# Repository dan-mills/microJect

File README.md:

# microJect
MQL lubrication system using automotive injectors to lubricate cutting tools.

Control is via modbus RTU on RS485 or via switches and pots (Two channels only in that mode). 
Power input is 24V and power delivered to the injector heads is 12V at up to about 3A total from an on board power converter. 

Firmware is written in Rust with Embassy as the framework and the processor on the board is an STM32F030k6. 

#Electrical Interface 
|           |         |
|----------|----------|
| Power supply | 24V @ 1.5A but usually much less.|
| Injector outputs | 12V @1A, 3A total max | 
| Digital inputs | 2 Opto isolated, 24V max |
| Analogue inputs | 2, 3.3V max, intended for potentiometers|
| Serial interface | Isolated RS485 |

# Operating modes
There is a 4 way dip switch on the board which configure the operating modes
| Switch | Function |
|--------|----------|
| 1 | Enables local control mode, the opto inputs and analog control the first two channels|
| 2| Modbus alternate address, sets the modbus address to be 9 instead of 8 |
| 3, 4| Modbus baud rate| 

Baud rates
| SW 3 | SW 4| Baud Rate |
|------|-----|-----------|
| Off | Off | 4800 |
| Off | On | 9600 |
| On | Off | 19200 |
| On | On | 115200 |

# Modbus support

Modbus interface is RTU over RS485 half duplex, formatted as 8-E-1.

Coils
| Coil | Description | 
|------|-------------|
| 1 | Pulse enable for channel 1|
| 2 | Pulse enable for channel 2|
| 3 | Pulse enable for channel 3|
| 4 | Pulse enable for channel 4|

Note in modbus mode the coils will switch off 5 seconds after the last communication is received to avoid spilling coolant everywhere. 

Holding Registers
| Register | Description |
|----------|-------------|
| 1 | Channel 1 pulse length |
| 2 | Channel 1 period |
| 3 | Channel 2 pulse length |
| 4 | Channel 2 period |
| 5 | Channel 3 pulse length |
| 6 | Channel 3 period |
| 7 | Channel 4 pulse length |
| 8 | Channel 4 period |

Discrete inputs
| Input | Description |
|-------|-------------|
| 1 | Enable input for ch1 when in local control mode|
| 2 | Enable input for ch2 when in local control mode|

Analogue inputs 
| Input | Description |
|-------|-------------|
| 1 | 0-3.3V period control input for channel 1 when in local control mode|
| 2 | 0-3.3V period control input for channel 2 when in local control mode|

Both the discrete inputs and the analogue channels can be read over modbus when not using local mode so you can readily use them for other things when using modbus for control.

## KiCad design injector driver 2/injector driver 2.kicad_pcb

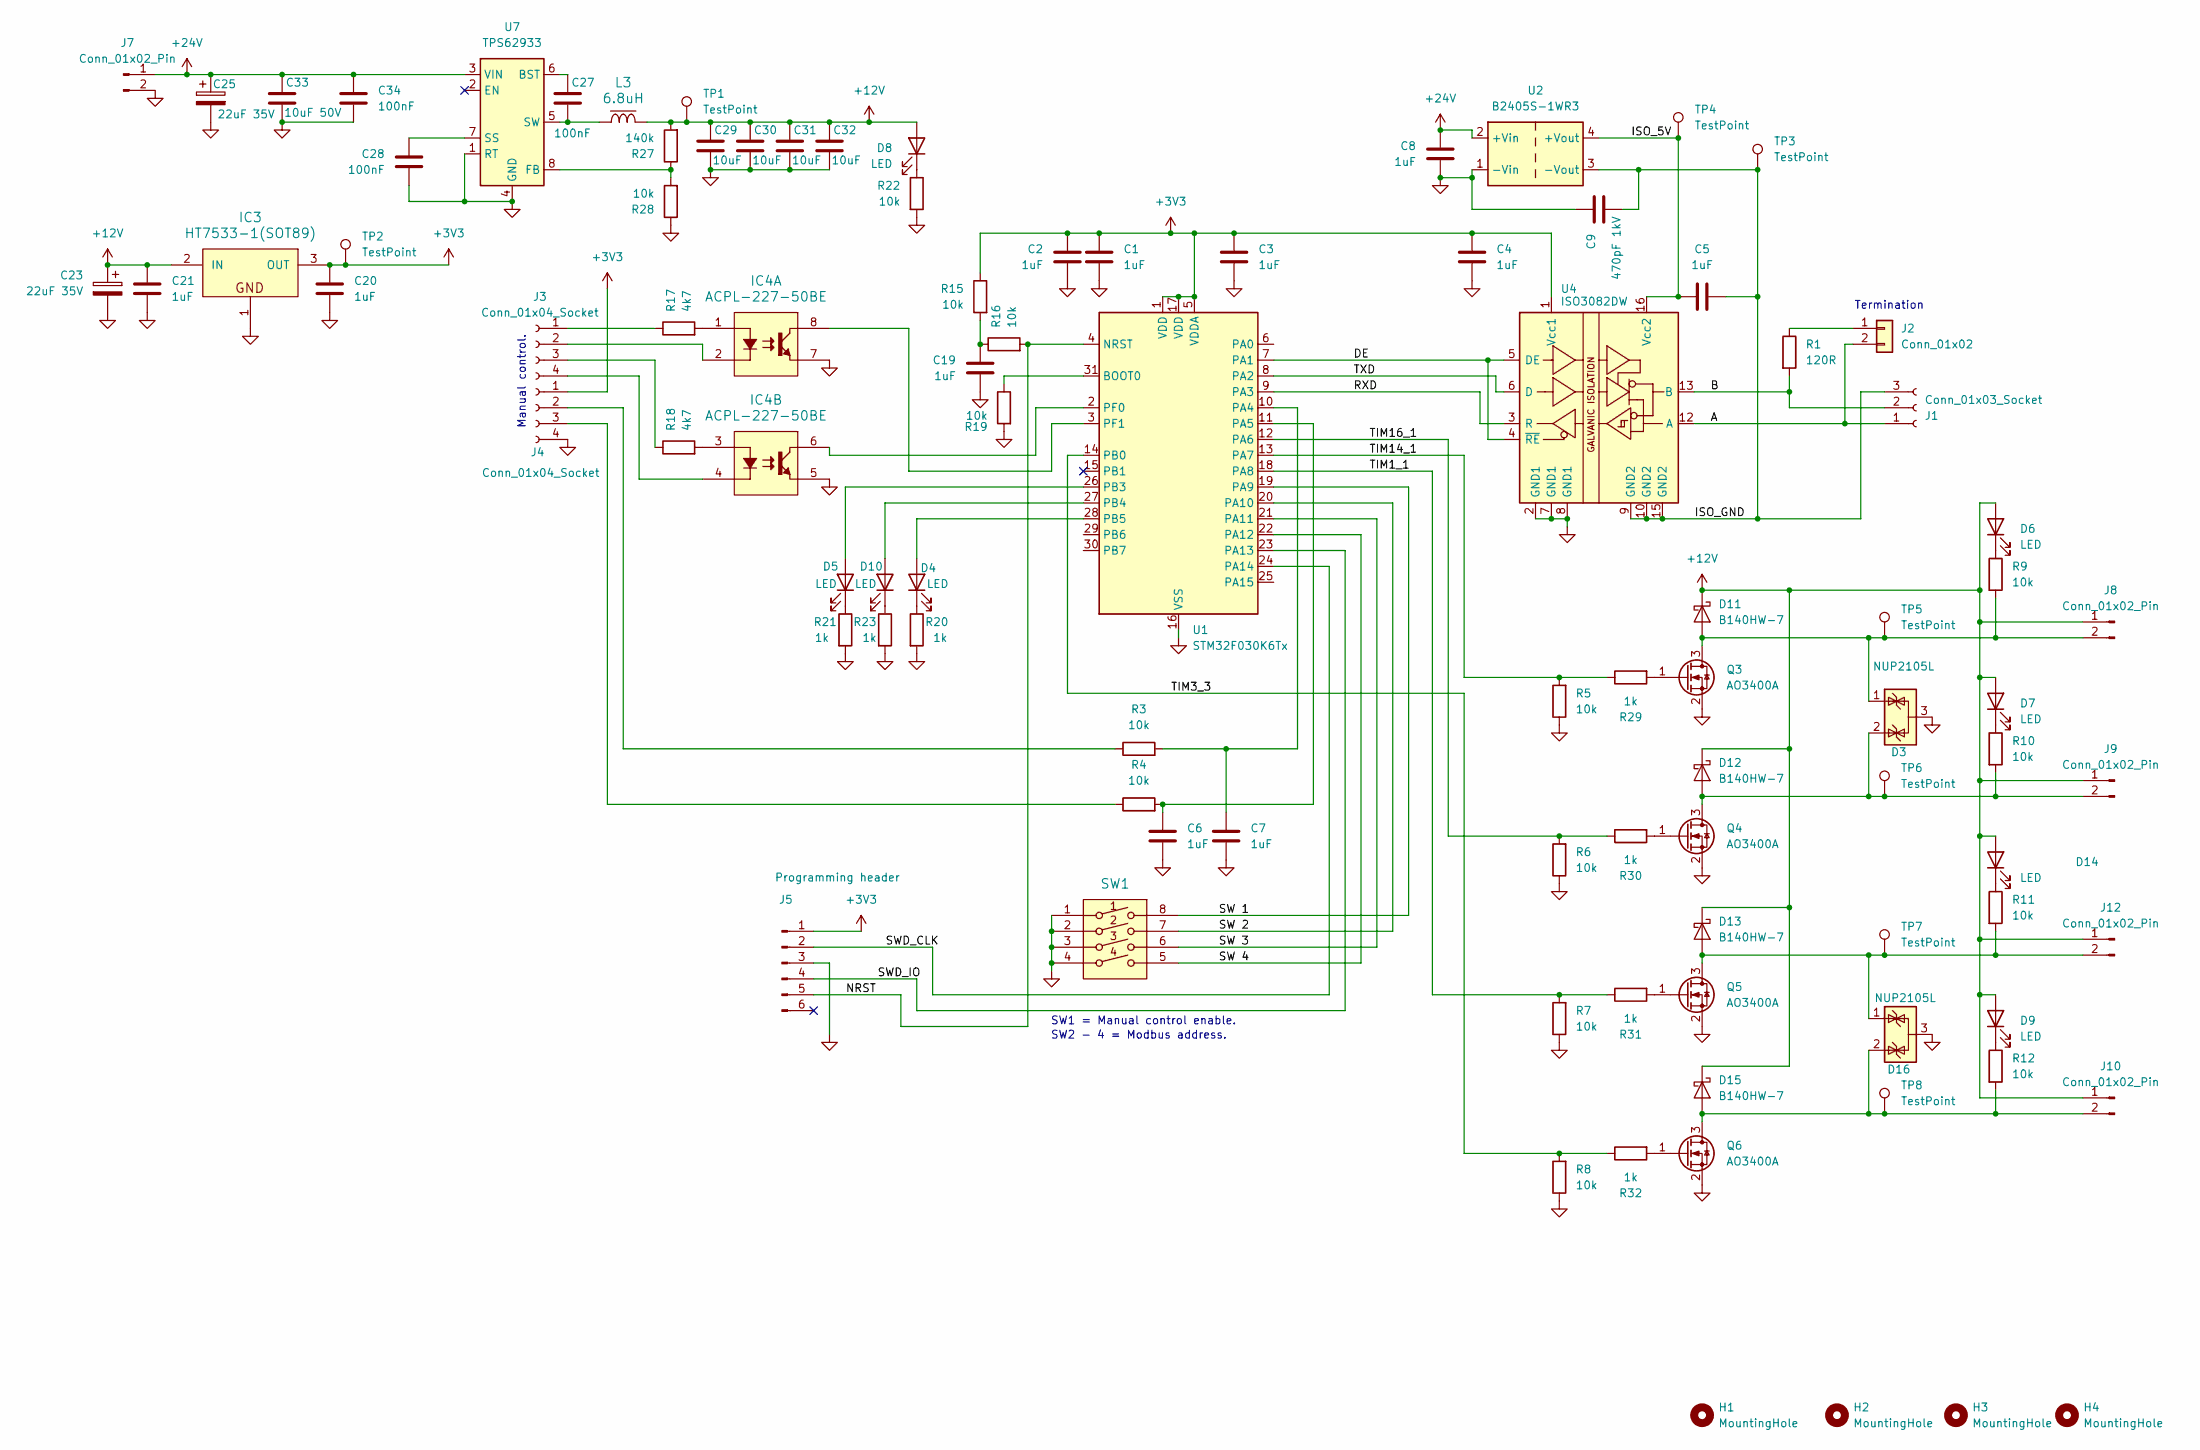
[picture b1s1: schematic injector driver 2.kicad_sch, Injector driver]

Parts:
C1, C2, C3, C4, C5, C6, C7, C8, C19, C20, C21: 1uF; C_0603_1608Metric
C9: 470pF 1kV; C_1206_3216Metric
C23, C25: 22uF 35V; CP_Elec_5x5.7
C27, C28, C34: 100nF; C_0603_1608Metric
C29, C30, C31, C32: 10uF; C_1206_3216Metric
C33: 10uF 50V; C_1206_3216Metric
D3, D16: NUP2105L; SOT-23
D4, D5, D6, D7, D8, D9, D10, D14: LED; LED_0603_1608Metric
D11, D12, D13, D15: B140HW-7; D_SOD-123; Part Number B140HW-7; JLCPCB ID C134429
H1, H2, H3, H4: MountingHole; MountingHole_3.2mm_M3_ISO14580_Pad
IC3: HT7533-1(SOT89); SOT89; Part Number HT7533-1(SOT89)
IC4: ACPL-227-50BE; SOIC127P700X220-8N; Part Description DC Input Dual Channel Half-Pitch Photot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
J1: Conn_01x03_Socket; PHOENIX_1751109
J2: Conn_01x02; PinHeader_1x02_P2.54mm_Vertical; Part Number 1-0201FBV0T
J3, J4: Conn_01x04_Socket; PHOENIX_1751112
J5: Programming header; PinHeader_1x06_P2.54mm_Vertical
J7, J8, J9, J10, J12: Conn_01x02_Pin; PHOENIX_1751099
L3: 6.8uH; IND_MURATA-PS_4500; Tolerance ±20%; Part Description Low Profile, High Current IHLP® Inductor
Q3, Q4, Q5, Q6: AO3400A; SOT-23
R1: 120R; R_1206_3216Metric
R3, R4, R5, R6, R7, R8, R9, R10, R11, R12, R15, R16, R19, R22, R28: 10k; R_0603_1608Metric
R17, R18: 4k7; R_0603_1608Metric
R20, R21, R23, R29, R30, R31, R32: 1k; R_0603_1608Metric
R27: 140k; R_0603_1608Metric
SW1: Switch; SW_DIPTRONICS_DHA-04TQ; Part Number SW_DIPTRONICS_DHA-04TQ
TP1, TP2, TP3, TP4, TP5, TP6, TP7, TP8: TestPoint; TestPoint_THTPad_2.5x2.5mm_Drill1.2mm
U1: STM32F030K6Tx; LQFP-32_7x7mm_P0.8mm
U2: B2405S-1WR3; Converter_DCDC_Murata_CRE1xxxxxx3C_THT
U4: ISO3082DW; SOIC-16W_7.5x10.3mm_P1.27mm
U7: TPS62933; SOT-583-8

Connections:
+3V3: C1.1, C2.1, C3.1, C4.1, C20.1, IC3.3 (OUT), J4.1, J5.1, R15.1, TP2.1 (1_1), U1.1 (VDD), U1.5 (VDDA), U1.17 (VDD), U4.1 (Vcc1)
+12V: C21.1, C23.1, C29.1, C30.1, C31.1, C32.1, D6.2 (A), D7.2 (A), D8.2 (A), D9.2 (A), D11.1 (K), D12.1 (K), D13.1 (K), D14.2 (A), D15.1 (K), IC3.2 (IN), J8.1, J9.1, J10.1, J12.1, L3.2, R27.2, TP1.1 (1_1)
+24V: C8.1, C25.1, C33.1, C34.1, J7.1, U2.2 (+Vin), U7.3 (VIN)
/A: J1.1, J2.2, U4.12 (A)
/B: J1.2, R1.2, U4.13 (B)
/DE: U1.7 (PA1), U4.4 (~RE), U4.5 (DE)
/ISO_5V: C5.1, TP4.1 (1_1), U2.4 (+Vout), U4.16 (Vcc2)
/ISO_GND: C5.2, C9.2, J1.3, TP3.1 (1_1), U2.3 (-Vout), U4.9 (GND2), U4.10 (GND2), U4.15 (GND2)
/NRST: J5.5, R16.2, U1.4 (NRST)
/RXD: U1.9 (PA3), U4.3 (R)
/SW 1: SW1.8, U1.19 (PA9)
/SW 2: SW1.7, U1.20 (PA10)
/SW 3: SW1.6, U1.21 (PA11)
/SW 4: SW1.5, U1.22 (PA12)
/SWD_CLK: J5.2, U1.24 (PA14)
/SWD_IO: J5.4, U1.23 (PA13)
/TIM1_1: R7.2, R31.1, U1.18 (PA8)
/TIM3_3: R8.2, R32.1, U1.14 (PB0)
/TIM14_1: R5.2, R29.1, U1.13 (PA7)
/TIM16_1: R6.2, R30.1, U1.12 (PA6)
/TXD: U1.8 (PA2), U4.6 (D)
GND: C1.2, C2.2, C3.2, C4.2, C6.2, C7.2, C8.2, C9.1, C19.2, C20.2, C21.2, C23.2, C25.2, C28.2, C29.2, C30.2, C31.2, C32.2, C33.2, C34.2, D3.3 (A), D16.3 (A), IC3.1 (GND), IC4.5 (E), IC4.7 (E), J4.4, J5.3, J7.2, Q3.2 (S), Q4.2 (S), Q5.2 (S), Q6.2 (S), R5.1, R6.1, R7.1, R8.1, R19.2, R20.2, R21.2, R22.2, R23.2, R28.1, SW1.1, SW1.2, SW1.3, SW1.4, U1.16 (VSS), U1.32 (VSS), U2.1 (-Vin), U4.2 (GND1), U4.7 (GND1), U4.8 (GND1), U7.1 (RT), U7.4 (GND)
unnamed: C19.1, R15.2, R16.1
unnamed: D4.2 (A), U1.28 (PB5)
unnamed: D4.1 (K), R20.1
unnamed: D5.2 (A), U1.26 (PB3)
unnamed: D5.1 (K), R21.1
unnamed: D6.1 (K), R9.1
unnamed: D7.1 (K), R10.1
unnamed: D8.1 (K), R22.1
unnamed: D9.1 (K), R12.1
unnamed: D10.2 (A), U1.27 (PB4)
unnamed: D10.1 (K), R23.1
unnamed: D3.1 (K), D11.2 (A), J8.2, Q3.3 (D), R9.2, TP5.1 (1_1)
unnamed: D3.2 (K), D12.2 (A), J9.2, Q4.3 (D), R10.2, TP6.1 (1_1)
unnamed: D13.2 (A), D16.1 (K), J12.2, Q5.3 (D), R11.2, TP7.1 (1_1)
unnamed: D14.1 (K), R11.1
unnamed: D15.2 (A), D16.2 (K), J10.2, Q6.3 (D), R12.2, TP8.1 (1_1)
unnamed: IC4.1 (A), R17.2
unnamed: IC4.8 (C), U1.3 (PF1)
unnamed: IC4.2 (K), J3.2
unnamed: IC4.3 (A), R18.2
unnamed: IC4.6 (C), U1.2 (PF0)
unnamed: IC4.4 (K), J3.4
unnamed: J2.1, R1.1
unnamed: J3.1, R17.1
unnamed: J3.3, R18.1
unnamed: J4.2, R3.1
unnamed: J4.3, R4.1
unnamed: Q3.1 (G), R29.2
unnamed: Q4.1 (G), R30.2
unnamed: Q5.1 (G), R31.2
unnamed: Q6.1 (G), R32.2
unnamed: R19.1, U1.31 (BOOT0)
unnamed: C7.1, R3.2, U1.10 (PA4)
unnamed: C6.1, R4.2, U1.11 (PA5)
unnamed: C27.1, U7.6 (BST)
unnamed: R27.1, R28.2, U7.8 (FB)
unnamed: C28.1, U7.7 (SS)
unnamed: C27.2, L3.1, U7.5 (SW)

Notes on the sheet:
SW1 = Manual control enable.
Termination
Manual control.
SW2 - 4 = Modbus address.

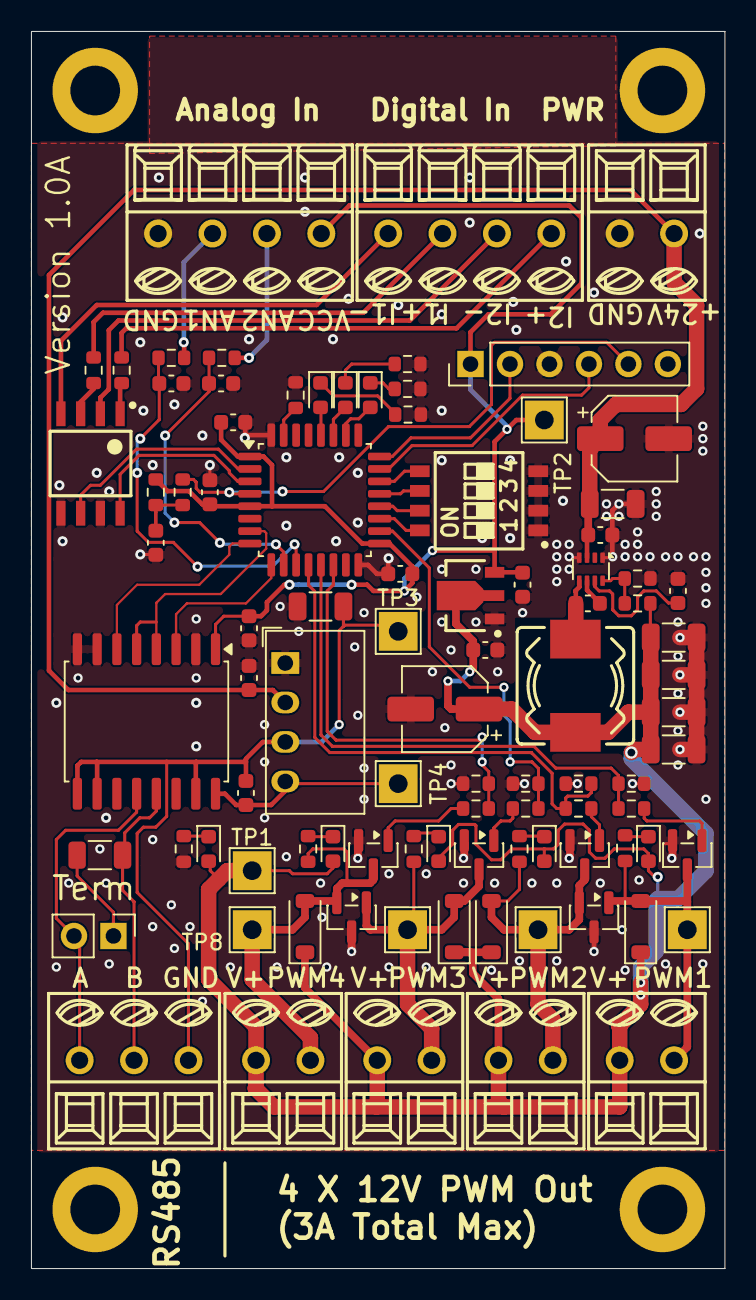
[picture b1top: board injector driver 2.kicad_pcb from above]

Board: 2 copper layers, 44.6 x 79.6 mm, 96 parts (0 on the bottom side), 60 nets.

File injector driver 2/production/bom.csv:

Designator,Footprint,Quantity,Value,LCSC Part #
"C1, C19, C2, C20, C21, C3, C4, C5, C6, C7, C8",0603,11,1uF,
"C23, C25",CP_Elec_5x5.7,2,22uF 35V,
"C27, C28, C34",0603,3,100nF,
"C29, C30, C31, C32",1206,4,10uF,
C33,1206,1,10uF 50V,
C9,1206,1,470pF 1kV,
"D10, D14, D4, D5, D6, D7, D8, D9",0603,8,LED,
"D11, D12, D13, D15",D_SOD-123,4,B140HW-7,
"D16, D3",SOT-23,2,NUP2105L,
IC3,SOT89,1,HT7533-1(SOT89),
IC4,SOIC127P700X220-8N,1,ACPL-227-50BE,
J1,PHOENIX_1751109,1,Conn_01x03_Socket,
"J10, J12, J7, J8, J9",PHOENIX_1751099,5,Conn_01x02_Pin,
J2,PinHeader_1x02_P2.54mm_Vertical,1,Conn_01x02,
"J3, J4",PHOENIX_1751112,2,Conn_01x04_Socket,
J5,PinHeader_1x06_P2.54mm_Vertical,1,Programming header,
L3,IND_MURATA-PS_4500,1,6.8uH,
"Q3, Q4, Q5, Q6",SOT-23,4,AO3400A,
R1,1206,1,120R,
"R10, R11, R12, R15, R16, R19, R22, R28, R3, R4, R5, R6, R7, R8, R9",0603,15,10k,
"R17, R18",0603,2,4k7,
"R20, R21, R23, R29, R30, R31, R32",0603,7,1k,
R27,0603,1,140k,
SW1,SW_DIPTRONICS_DHA-04TQ,1,Switch,
"TP1, TP2, TP3, TP4, TP5, TP6, TP7, TP8",TestPoint_THTPad_2.5x2.5mm_Drill1.2mm,8,TestPoint,
U1,LQFP-32_7x7mm_P0.8mm,1,STM32F030K6Tx,
U2,Converter_DCDC_Murata_CRE1xxxxxx3C_THT,1,B2405S-1WR3,
U4,SOIC-16W_7.5x10.3mm_P1.27mm,1,ISO3082DW,
U7,SOT-583-8,1,TPS62933,

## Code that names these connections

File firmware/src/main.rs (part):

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async fn input_read(
    adc: Peri<'static, peripherals::ADC1>,
    dma: Peri<'static, peripherals::DMA1_CH1>,
    adc_pin0: Peri<'static, peripherals::PA4>, //ADC input 1
    adc_pin1: Peri<'static, peripherals::PA5>, //ADC input 2
    opto_pin0: Peri<'static, AnyPin>,          // Opto input 1
    opto_pin1: Peri<'static, AnyPin>,          // Opto input 2
    local_control: bool, // True if local switches and pots are being used to control the output
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    // UART Clock
    cnf.rcc.mux.usart1sw = embassy_stm32::rcc::mux::Usart1sw::Sys;
    let p = embassy_stm32::init(cnf);
    let sw1 = Input::new(p.PA9, Pull::Up); // SW1 selects if modbus should be overridden by the analog and opto inputs
    let sw2 = Input::new(p.PA10, Pull::Up); // Alternate modbus address
    let sw3 = Input::new(p.PA11, Pull::Up); // Baud rate select MSB
    let sw4 = Input::new(p.PA12, Pull::Up); // Baud rate select LSB

    // USART Configuration
    let mut rate = 0;
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    usart_config.de_config = embassy_stm32::usart::OutputConfig::PushPull;
    let usart = Uart::new_with_de(
        p.USART1,
        p.PA2,
        p.PA3,
        p.PA1,
        p.DMA1_CH2,
        p.DMA1_CH5,
        Irqs,
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        defmt::info!("Overriding modbus input with local inputs");
    }

    let mut led1 = Output::new(p.PB3, Level::Low, Speed::Low);
    let led2 = Output::new(p.PB4, Level::Low, Speed::Low);
    let led3 = Output::new(p.PB5, Level::Low, Speed::Low);

    let mut pwm_pins = [
        Output::new(p.PA7, Level::Low, Speed::Low),
        Output::new(p.PA6, Level::Low, Speed::Low),
        Output::new(p.PA8, Level::Low, Speed::Low),
        Output::new(p.PB0, Level::Low, Speed::Low),
    ];
    // Kick off the ADC and GPI task
    spawner.spawn(
        input_read(
            p.ADC1,
            p.DMA1_CH1,
            p.PA4,
            p.PA5,
            p.PF1.into(),
            p.PF0.into(),
            sw1.is_low(),
        )
        .unwrap(),
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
